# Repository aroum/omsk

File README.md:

# OMSK

OMSK is an experimental, pocket-sized hardware platform designed primarily (but not exclusively) for custom synthesizer firmware development. Built around the RP2350-Zero microcontroller module, OMSK packs an exceptional density of tactile controls, audio routing, and visual indicators into a highly portable footprint.

## Hardware Features

- **MCU:** RP2350-Zero module (or RP2040-Zero)
- **Controls:**
  - 4x4 matrix of Kailh Choc v2 mechanical switches (supports hot-swap sockets)
  - 4 rotary encoders (Alps EC12)
- **Display:** 128x64 OLED screen (supports SH1107 or SSD1312 via I2C)
- **Visuals:** 22 addressable RGB LEDs (WS2812B MINI-E) for parameter tracking and custom animations
- **Audio & Connectivity:**
  - Built-in mono PWM audio output (with optional onboard headphone amplifier circuit)
  - Classic hardware MIDI In/Out jacks (TRS Type A)
  - USB MIDI class-compliant device interface
  - Support for an optional external PCM5102 I2S DAC for high-fidelity stereo audio

For more details on assembly, schematic routing, and BOM, see the [Hardware PCB Guide](hardware/pcb/README.md) and [3D Case/Enclosure Design](hardware/case/README.md).

## Bare-metal Software

All official firmware is written in pure C/C++ using the native Raspberry Pi Pico SDK. There is no Arduino overhead and no RTOS, ensuring maximum CPU availability, bare-metal performance, and sub-millisecond audio and MIDI latency.

### Architecture

Rather than compiling a single monolithic application, OMSK uses separate firmware files for different applications. This separation is dictated by hardware memory limits and fundamental architectural differences:

- Synthesizer engines require different memory structures (e.g., flash space allocated for wavetables and filter LUTs vs. granular sample buffers).
- Audio paths, envelopes, and modulation matrices differ completely between engines.

All firmware targets share a unified low-level core library located in [firmware/shared](firmware/shared), but compile as independent binaries.

> [!NOTE]
> Each firmware folder contains its own documentation and parameter reference: see the respective `README.md` (e.g., [omsk_fm/README.md](firmware/omsk_fm/README.md)) and the `docs/` directory for detailed configuration options (e.g., [omsk_fm/docs](firmware/omsk_fm/docs)). Shared hardware pinouts and peripheral configurations are defined in [firmware/shared/hw_config.h](firmware/shared/hw_config.h) (see [firmware/shared/README.md](firmware/shared/README.md)).

### Firmwares

Explore the firmware directory at [firmware](firmware) to flash any of the following targets:

- **[omsk_wave](firmware/omsk_wave):** A polyphonic wavetable synthesizer featuring deep modulation routing, resonant filters, and non-volatile patch storage.
- **[omsk_grain](firmware/omsk_grain):** A 4-voice granular synthesizer offering real-time grain manipulation, modulation matrices, and full MIDI control.
- **[omsk_fm](firmware/omsk_fm):** An FM (Frequency Modulation) synthesizer engine.
- **[omsk_tracker](firmware/omsk_tracker):** A pocket music tracker and step sequencer to compose patterns and songs directly on the device. [planned]
- **DMK:** A customizable mechanical macropad firmware featuring full Vial compatibility. Remap keys, layout layers, macros, and rotary encoder actions directly from your web browser.
- **[omsk_midi](firmware/omsk_midi):** A simple demonstration firmware that configures the device as a class-compliant USB/TRS MIDI controller.
- **[omsk_oled_test](firmware/omsk_oled_test):** A diagnostic utility to test OLED display functionality, address configuration, and graphics rendering.

Both synth engines support full MIDI CC mapping and preset saving directly to the onboard non-volatile memory.

## Desktop Simulators & Tools

The [`desktop`](desktop) directory contains Python-based software simulators, hardware emulators, and firmware development utilities managed via [`uv`](https://github.com/astral-sh/uv):

- **[`desktop/grain_simulator`](desktop/grain_simulator):** PySide6 GUI simulation of the OMSK Granular Synth engine (`omsk_grain`).
- **[`desktop/synth_simulator`](desktop/synth_simulator):** PySide6 GUI simulation of the OMSK Analog/Wavetable Synth engine (`omsk_synth`).
- **[`desktop/synth_tools`](desktop/synth_tools):** Firmware LUT header generators, hardware emulators (128x64 OLED display, 4x4 matrix keypad), and interactive web testbenches.

Quick launch:

```bash
cd desktop
uv sync
uv run synth_simulator/main.py
```

For more details, see the [Desktop README](desktop/README.md).

## Roadmap & Status

This project is currently a work in progress.

- **Hardware:** Case and knob designs are being actively iterated.
- **Software:** A dedicated web-based editor using WebMIDI is planned to allow quick parameter tweaking, firmware updates, and preset backup/sharing.

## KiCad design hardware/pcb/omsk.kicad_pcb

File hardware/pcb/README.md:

# PCB

## BOM

### Basic

| name                              |  pcs | type          | package | position          | description                      |
| --------------------------------- | ---: | ------------- | ------- | ----------------- | -------------------------------- |
| 1N4148W                           |   17 | Diode         | SOD-323 | D1 - D17          | keyboard matrix + MIDI           |
| 100nF x7r 50v                     |    4 | Capacitor     | 0805    | C1, C3, C4, C5    | MIDI jacks + PWM Audio           |
| 47uF x7r 50v                      |    1 | Capacitor     | 1210    | C2                | PWM audio                        |
| 10R for 3v3 or 220 Ohm for 5v out |    1 | Resistor      | 0603    | R4                | MIDI jacks                       |
| 33R for 3v3 or 220 Ohm for 5v out |    1 | Resistor      | 0603    | R3                | MIDI jacks                       |
| 100R                              |    1 | Resistor      | 0603    | R6                | PWM audio                        |
| 220R                              |    2 | Resistor      | 0603    | R1, R5            | PWM audio + MIDI jacks           |
| 470R                              |    1 | Resistor      | 0603    | R2                | MIDI jacks                       |
| 1.8k                              |    1 | Resistor      | 0603    | R7                | PWM audio                        |
| PJ-313 (3 color)                  |    3 | jack sockets  | THD     | J2, J3, J4        | Audio + MIDI jacks               |
| Alps EC12 8.5 mm                  |    4 | Encoder       | THD     | ROTENC1 - ROTENC4 | Encoder for more info view below |
| H11L1 SMD                         |    1 | Optocoupler   | SOP-6   | U1                | MIDI jacks                       |
| Kailh choc sockets                |   16 | Switch socket | SMD     | SW1 - SW16        | keyboard                         |
| Kailh choc v2                     |   16 | Switch        | THD     | SW1 - SW16        | keyboard                         |
| NC7WZ16P6X                        |    1 | IC            | SC-70-6 | U2                | MIDI jacks + PWM audio           |
| rp2040/rp2350 zero                |    1 | MCU           | Module  | MCU1              | MCU (rp2350 recomended)          |
| WS2812B MINI-E                    |   22 | RGB LED       | 3228SMD | LED1 - LED22      | WS2812B MINI-E                   |

#### Encoders

You can choose any one of the following encoder models:

| name         | torque                 | # of detent/pulses | description |
| ------------ | ---------------------- | -----------------: | ----------- |
| EC12E1220301 | Standard 3 to 20mN･m   |                 12 |             |
| EC12E1240301 | Lightest (jog) 3±2mN･m |                 12 |             |
| EC12E2420301 | Standard 3 to 20mN･m   |                 24 | recommended |
| EC12E2440301 | Lightest (jog) 3±2mN･m |                 24 | recommended |

### Extra

| name                            |  pcs | type    | package | description                                                    |
| ------------------------------- | ---: | ------- | ------- | -------------------------------------------------------------- |
| MIDI cable (DIN5 M to jack 3.5) |    1 | Cable   | Cable   | TRS to DIN5 MIDI cable (Type A) for use external MIDI hardware |
| YS-SK6812MINI-E                 |   22 | RGB LED | 3228SMD | RGB LEDs                                                       |

#### OLED

You can choose any one of the following display models:

| name                             | pcs | type    | package | description |
| -------------------------------- | --- | ------- | ------- | ----------- |
| TZT 1.3" OLED 64×128 i2c SSD1312 | 1   | Display | Module  |             |
| TZT 1.3" OLED 64×128 i2c SH1107  | 1   | Display | Module  | recommended |

##### Pins

| Module pin | MCU pin |
| ---------- | ------- |
| **GND**    | GND     |
| **VCC**    | 3.3V    |
| **SDA**    | GPIO20  |
| **SCL**    | GPIO21  |

#### Headphone amp

Formally, you should not connect headphones directly to the DAC or PWM output without an amplifier; however, in practice, it works fine directly, making an amplifier highly optional. If you decide to use one, you can choose any of the following headphone amplifier models:

| IC                | mW    | size  | price | description |
| ----------------- | ----- | ----- | ----- | ----------- |
| TPA6132           | 25    | S     | 90    |             |
| TDA1308           | 40-80 | S     | 71    |             |
| MAX4410           | 80    | M     | 157   |             |
| MAX97220 +++      | 125   | 20x24 | 225   | tested      |
| OPA1622           | 145   | L     | 113   |             |
| LM4881            | 150   | M     | 60    |             |
| TPA6112 & SGM4812 | 150   | M     | 183   |             |

#### DAC

GY-PCM5102 I2S PCM5102A module

##### Pins

| Module pin | MCU pin / Connection                                        |
| ---------- | ----------------------------------------------------------- |
| **GND**    | GND                                                         |
| **VCC**    | 5V                                                          |
| **BCK**    | GPIO17                                                      |
| **LRCK**   | GPIO18                                                      |
| **DIN**    | GPIO19                                                      |
| **SCK**    | GND (solder jumper next to SCK pin or wire to GND)          |

## Build guide

- Solder all components starting from the lowest profile to the highest in the following order:
  - Diodes
  - Hotswap sockets
  - RGB LEDs
  - For NC7WZ16P6X (U2): the Pin 1 indicator on the IC consists of two dots on the bottom side (where the leftmost dot marks Pin 1), which aligns with the silkscreen tick mark on the PCB footprint.
  - Resistors
  - Capacitors
  - Jacks (recommended colors: green for MIDI IN, yellow for MIDI OUT, black for Audio OUT)
  - H11L1 (U1): the Pin 1 indicator on the IC is a dot on the bottom side, which aligns with the silkscreen tick mark on the PCB footprint.
  - Encoders
  - Solder two jumpers on the board to the `LINE` position (if you plan to use PWM audio).
  - Solder the `5V/3V3` jumper to the required position. This jumper controls the supply voltage of the NC7WZ16P6X (U2) IC. This affects the voltage of the MIDI OUT jack (for 5V, you must change resistors R3-R4 to 220 Ohm) and the PWM audio output level (5V increases the volume significantly, but might introduce noise from the USB power line).
- Connect external modules if needed:
  - **DAC**
    - Solder the jumpers on the back of the module: 1L, 2L, 3H, 4L
    - Solder the jumper bridge next to the SCK pin on the module (bridges SCK to GND to enable internal PLL for 3-wire I2S)
    - Desolder or cut off the audio jack from the module, as it takes too much space and won't fit in the case.
    - Connect using wires:
      - GND on the module to GND on the PCB
      - LOUT on the module to JACK L OUT on the PCB
      - ROUT on the module to JACK R OUT on the PCB
      - VIN to 5V
      - LRCK to GPIO18
      - DIN to GPIO19
      - BCK to GPIO17
      - Solder two jumpers on the board to the `AMP` position
  - **OLED**
    - GND to GND
    - VCC to 3.3V
    - SDA to GPIO20
    - SCL to GPIO21
  - **Headphone amp**
    - GND
    - VCC to 3.3V
    - L- to GND
    - R- to GND
    - L+ to the audio source PWM/DAC LEFT CHANNEL
    - R+ to the audio source PWM/DAC RIGHT CHANNEL
    - LOUT to the audio jack OUT LEFT CHANNEL
    - ROUT to the audio jack OUT RIGHT CHANNEL
    - Solder two jumpers on the board to the `AMP` position
- Assemble the device into the case
- Flash the required firmware

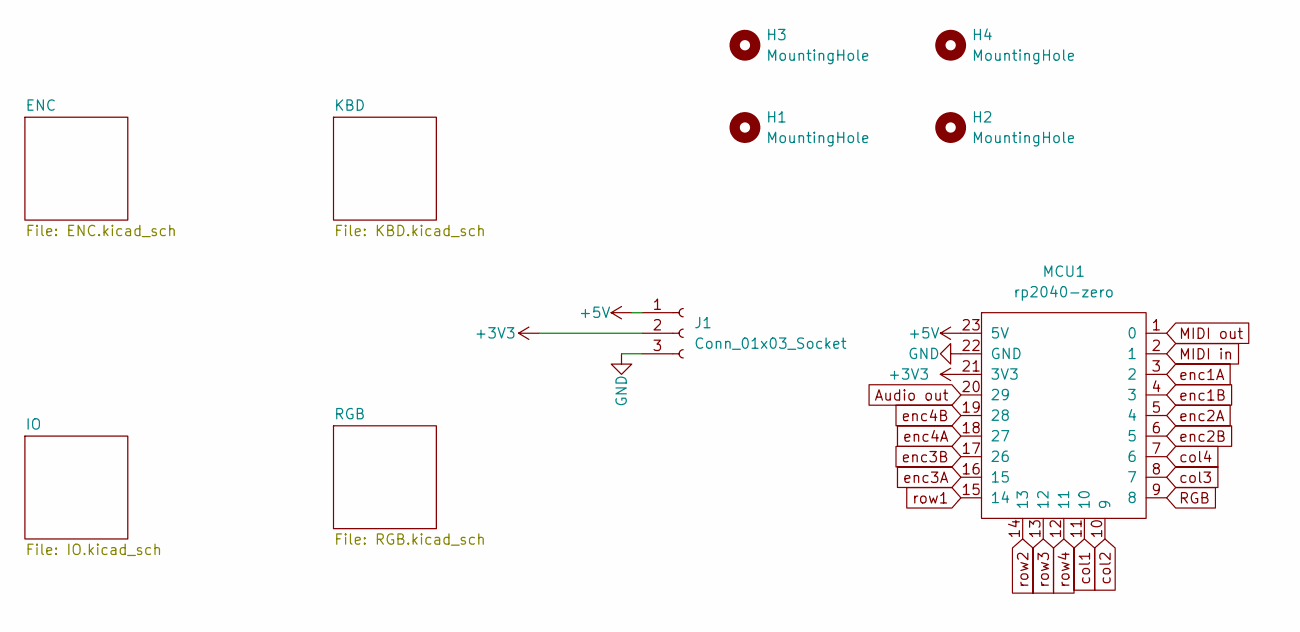
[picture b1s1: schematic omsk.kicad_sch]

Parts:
H1, H2, H3, H4: MountingHole
J1: Conn_01x03_Socket; PinHeader_1x03_P2.54mm_Vertical
MCU1: rp2040-zero; MCU_rp2040-zero

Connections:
+3V3: J1.2, MCU1.21 (3V3); also elsewhere on the board
+5V: J1.1, MCU1.23 (5V); also elsewhere on the board
Audio out: MCU1.20 (29); also elsewhere on the board
GND: J1.3, MCU1.22 (GND); also elsewhere on the board
MIDI in: MCU1.2 (1); also elsewhere on the board
MIDI out: MCU1.1 (0); also elsewhere on the board
RGB: MCU1.9 (8); also elsewhere on the board
col1: MCU1.11 (10); also elsewhere on the board
col2: MCU1.10 (9); also elsewhere on the board
col3: MCU1.8 (7); also elsewhere on the board
col4: MCU1.7 (6); also elsewhere on the board
enc1A: MCU1.3 (2); also elsewhere on the board
enc1B: MCU1.4 (3); also elsewhere on the board
enc2A: MCU1.5 (4); also elsewhere on the board
enc2B: MCU1.6 (5); also elsewhere on the board
enc3A: MCU1.16 (15); also elsewhere on the board
enc3B: MCU1.17 (26); also elsewhere on the board
enc4A: MCU1.18 (27); also elsewhere on the board
enc4B: MCU1.19 (28); also elsewhere on the board
row1: MCU1.15 (14); also elsewhere on the board
row2: MCU1.14 (13); also elsewhere on the board
row3: MCU1.13 (12); also elsewhere on the board
row4: MCU1.12 (11); also elsewhere on the board

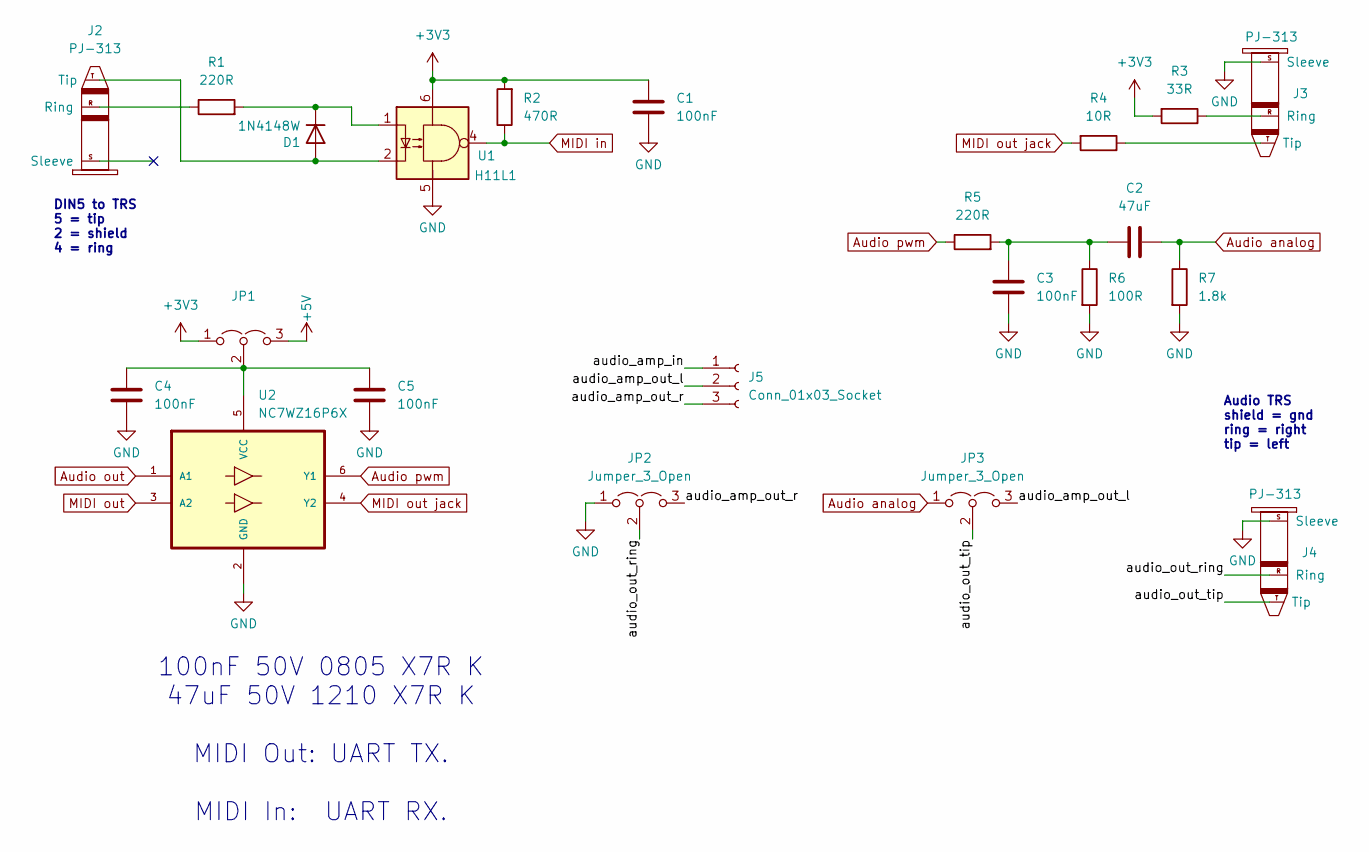
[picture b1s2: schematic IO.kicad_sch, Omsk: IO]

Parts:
C1, C3, C4, C5: 100nF; C_0805_2012Metric_Pad1.18x1.45mm_HandSolder
C2: 47uF; C_1210_3225Metric_Pad1.33x2.70mm_HandSolder
D1: 1N4148W; D_SOD-323_1side
J2, J3, J4: PJ-313; JACK_PJ-313A_1side
J5: Conn_01x03_Socket; PinHeader_1x03_P2.54mm_Vertical
JP1, JP2, JP3: Jumper_3_Open; SolderJumper-3_P1.3mm_Open_RoundedPad1.0x1.5mm
R1, R5: 220R; R_0603_1608Metric_1side
R2: 470R; R_0603_1608Metric_1side
R3: 33R; R_0603_1608Metric_1side
R4: 10R; R_0603_1608Metric_1side
R6: 100R; R_0603_1608Metric_1side
R7: 1.8k; R_0603_1608Metric_1side
U1: H11L1; DIP-6_W8.89mm_SMDSocket_LongPads
U2: NC7WZ16P6X; SOT65P210X110-6N; MPN NC7WZ16P6X

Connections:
+3V3: C1.1, JP1.1 (A), R2.2, R3.2, U1.6; also elsewhere on the board
+5V: JP1.3 (B); also elsewhere on the board
/IO/audio_amp_in: J5.1
/IO/audio_amp_out_l: J5.2, JP3.3 (B)
/IO/audio_amp_out_r: J5.3, JP2.3 (B)
/IO/audio_out_ring: J4.R (Ring), JP2.2 (C)
/IO/audio_out_tip: J4.T (Tip), JP3.2 (C)
Audio analog: C2.2, JP3.1 (A), R7.1
Audio out: U2.1 (A1); also elsewhere on the board
Audio pwm: R5.1, U2.6 (Y1)
GND: C1.2, C3.1, C4.2, C5.2, J3.S (Sleeve), J4.S (Sleeve), JP2.1 (A), R6.2, R7.2, U1.5, U2.2 (GND); also elsewhere on the board
MIDI in: R2.1, U1.4; also elsewhere on the board
MIDI out: U2.3 (A2); also elsewhere on the board
MIDI out jack: R4.2, U2.4 (Y2)
unnamed: C2.1, C3.2, R5.2, R6.1
unnamed: D1.2 (A), J2.T (Tip), U1.2
unnamed: D1.1 (K), R1.2, U1.1
unnamed: J2.R (Ring), R1.1
unnamed: J3.R (Ring), R3.1
unnamed: J3.T (Tip), R4.1
unnamed: C4.1, C5.1, JP1.2 (C), U2.5 (VCC)

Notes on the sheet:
DIN5 to TRS 5 = tip 2 = shield 4 = ring
100nF 50V 0805 X7R K 47uF 50V 1210 X7R K MIDI Out: UART TX. MIDI In: UART RX.
Audio TRS shield = gnd ring = right tip = left

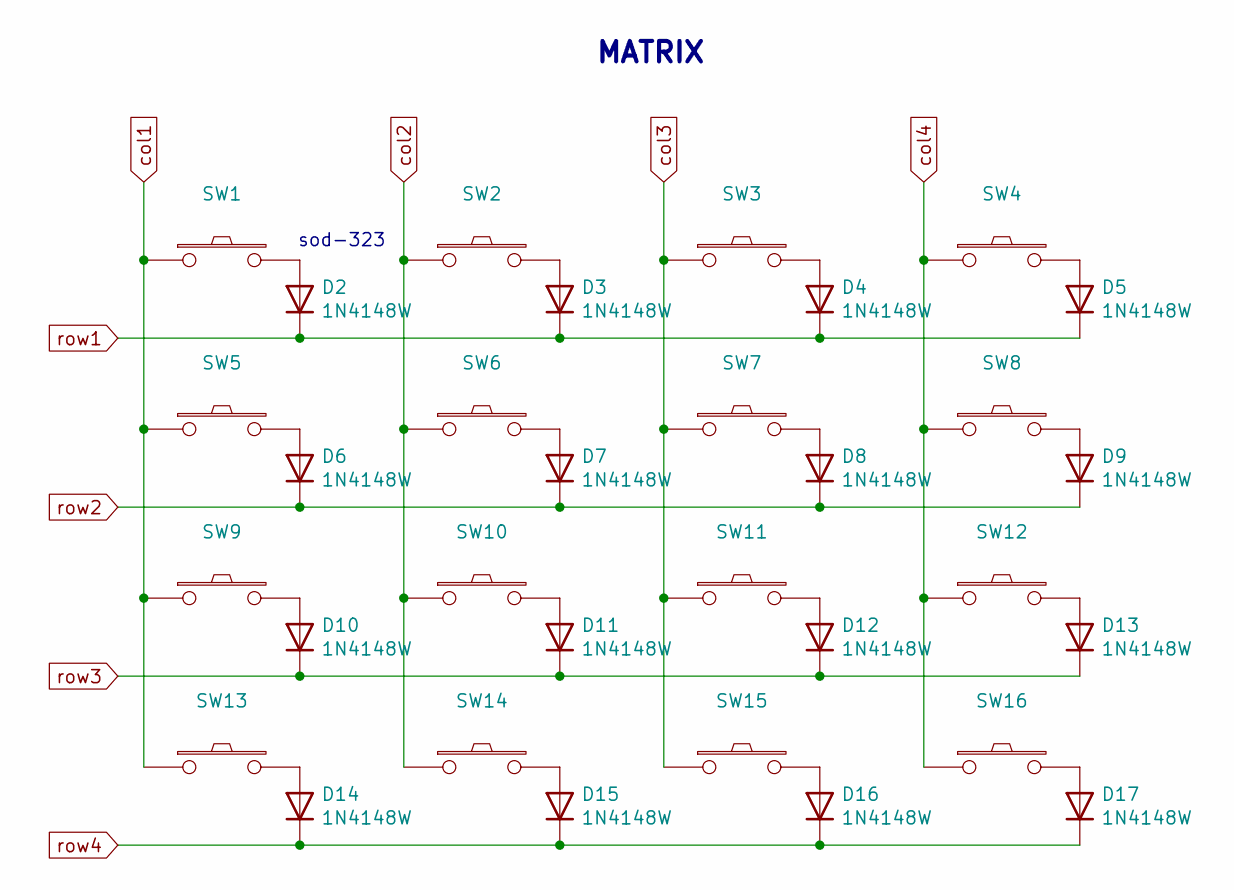
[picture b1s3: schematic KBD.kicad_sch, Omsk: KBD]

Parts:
D2, D3, D4, D5, D6, D7, D8, D9, D10, D11, D12, D13, D14, D15, D16, D17: 1N4148W; D_SOD-323_1side
SW1, SW2, SW3, SW4, SW5, SW6, SW7, SW8, SW9, SW10, SW11, SW12, SW13, SW14, SW15, SW16: SW_PUSH; SW_choc12_hotswap

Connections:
unnamed: D2.2 (A), SW1.2
unnamed: D3.2 (A), SW2.2
unnamed: D4.2 (A), SW3.2
unnamed: D5.2 (A), SW4.2
unnamed: D6.2 (A), SW5.2
unnamed: D7.2 (A), SW6.2
unnamed: D8.2 (A), SW7.2
unnamed: D9.2 (A), SW8.2
unnamed: D10.2 (A), SW9.2
unnamed: D11.2 (A), SW10.2
unnamed: D12.2 (A), SW11.2
unnamed: D13.2 (A), SW12.2
unnamed: D14.2 (A), SW13.2
unnamed: D15.2 (A), SW14.2
unnamed: D16.2 (A), SW15.2
unnamed: D17.2 (A), SW16.2
col1: SW1.1, SW5.1, SW9.1, SW13.1; also elsewhere on the board
col2: SW2.1, SW6.1, SW10.1, SW14.1; also elsewhere on the board
col3: SW3.1, SW7.1, SW11.1, SW15.1; also elsewhere on the board
col4: SW4.1, SW8.1, SW12.1, SW16.1; also elsewhere on the board
row1: D2.1 (K), D3.1 (K), D4.1 (K), D5.1 (K); also elsewhere on the board
row2: D6.1 (K), D7.1 (K), D8.1 (K), D9.1 (K); also elsewhere on the board
row3: D10.1 (K), D11.1 (K), D12.1 (K), D13.1 (K); also elsewhere on the board
row4: D14.1 (K), D15.1 (K), D16.1 (K), D17.1 (K); also elsewhere on the board

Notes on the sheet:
sod-323
MATRIX

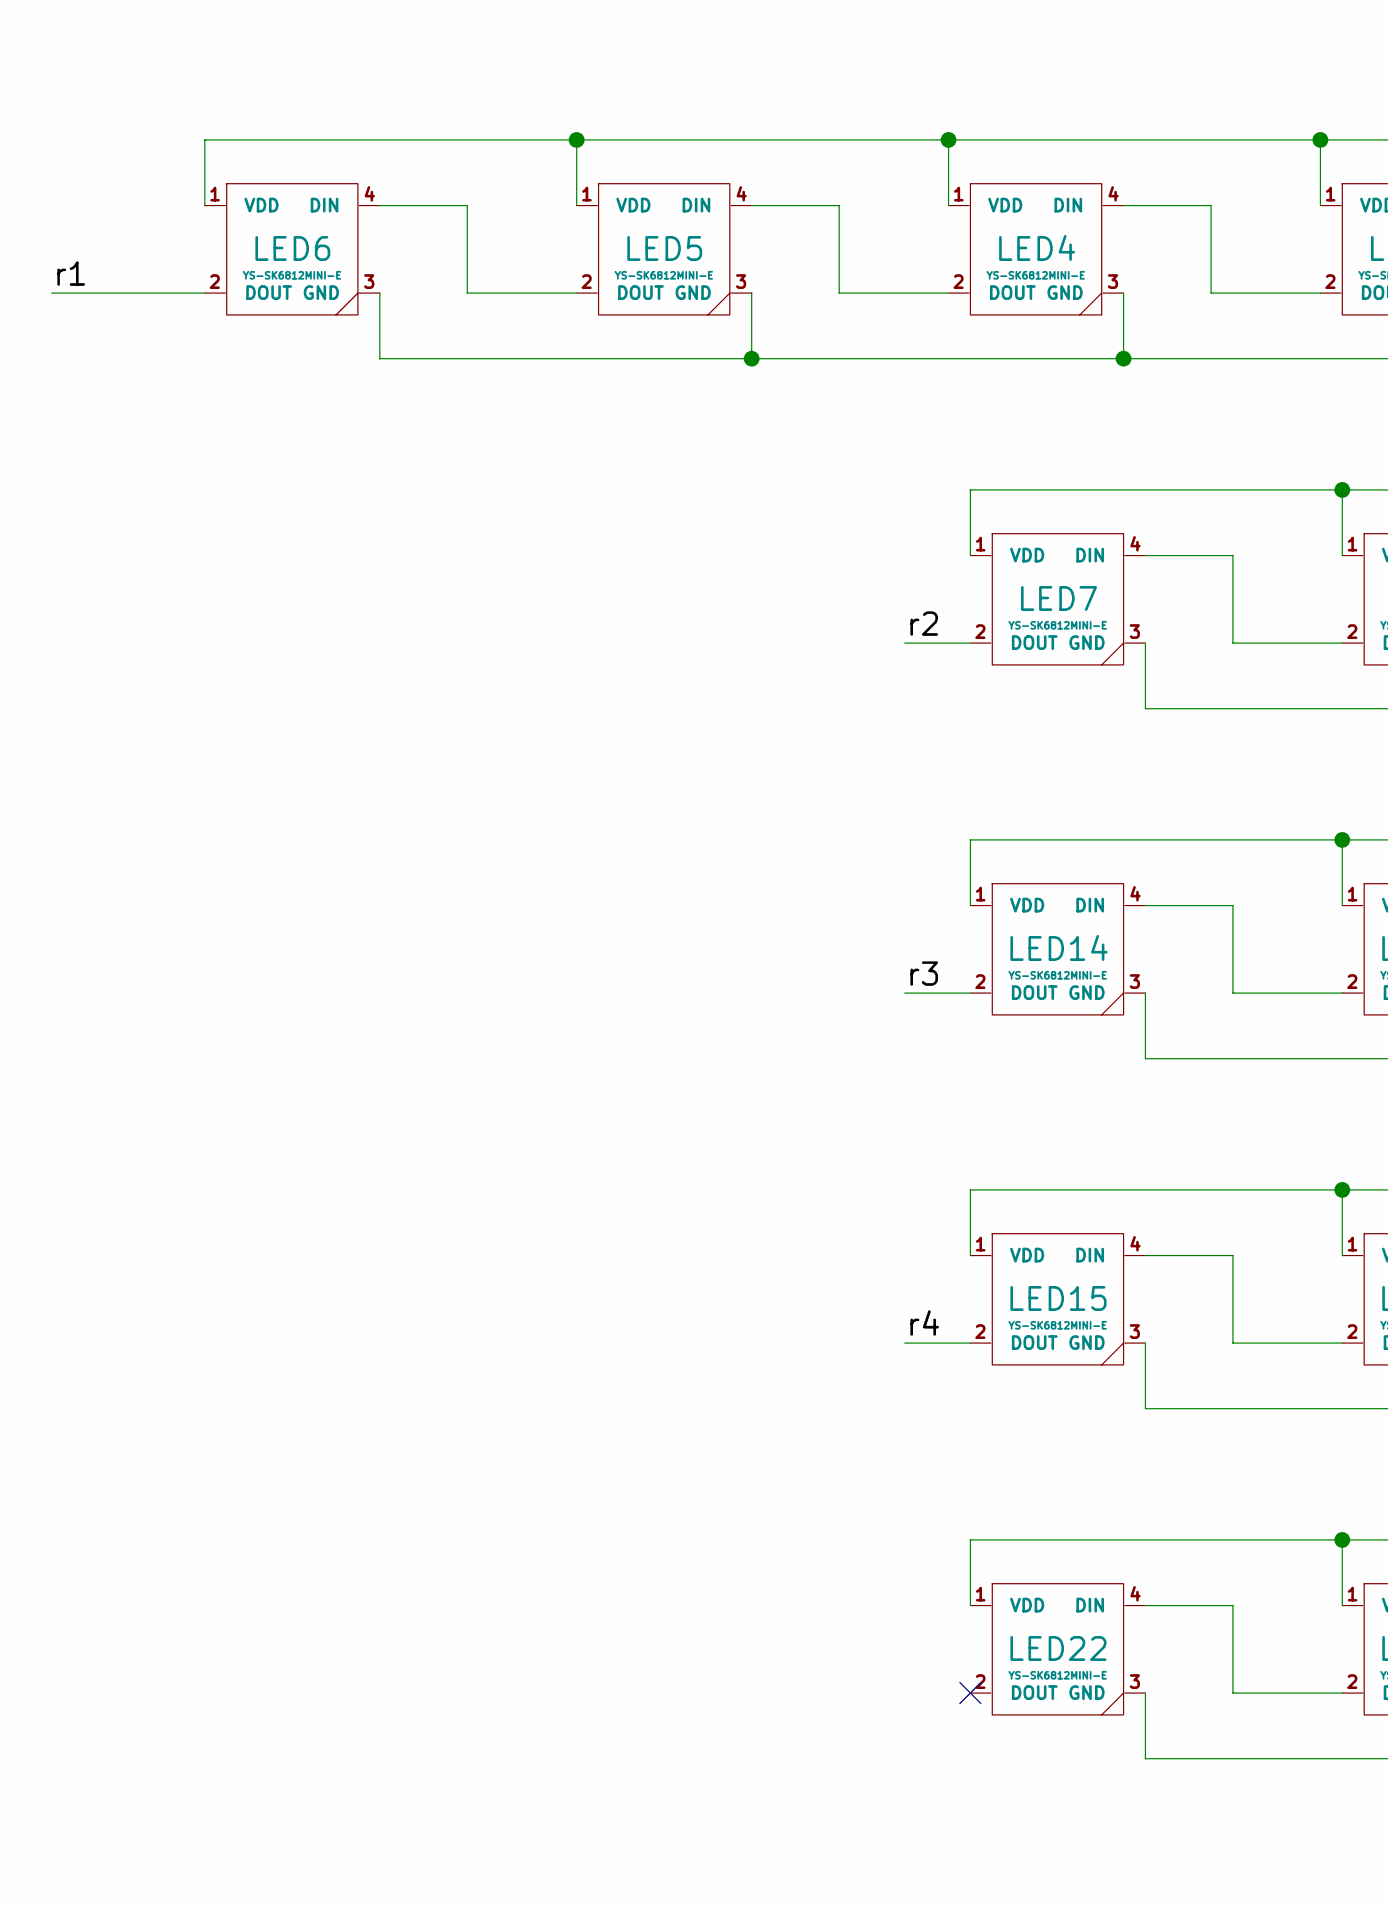
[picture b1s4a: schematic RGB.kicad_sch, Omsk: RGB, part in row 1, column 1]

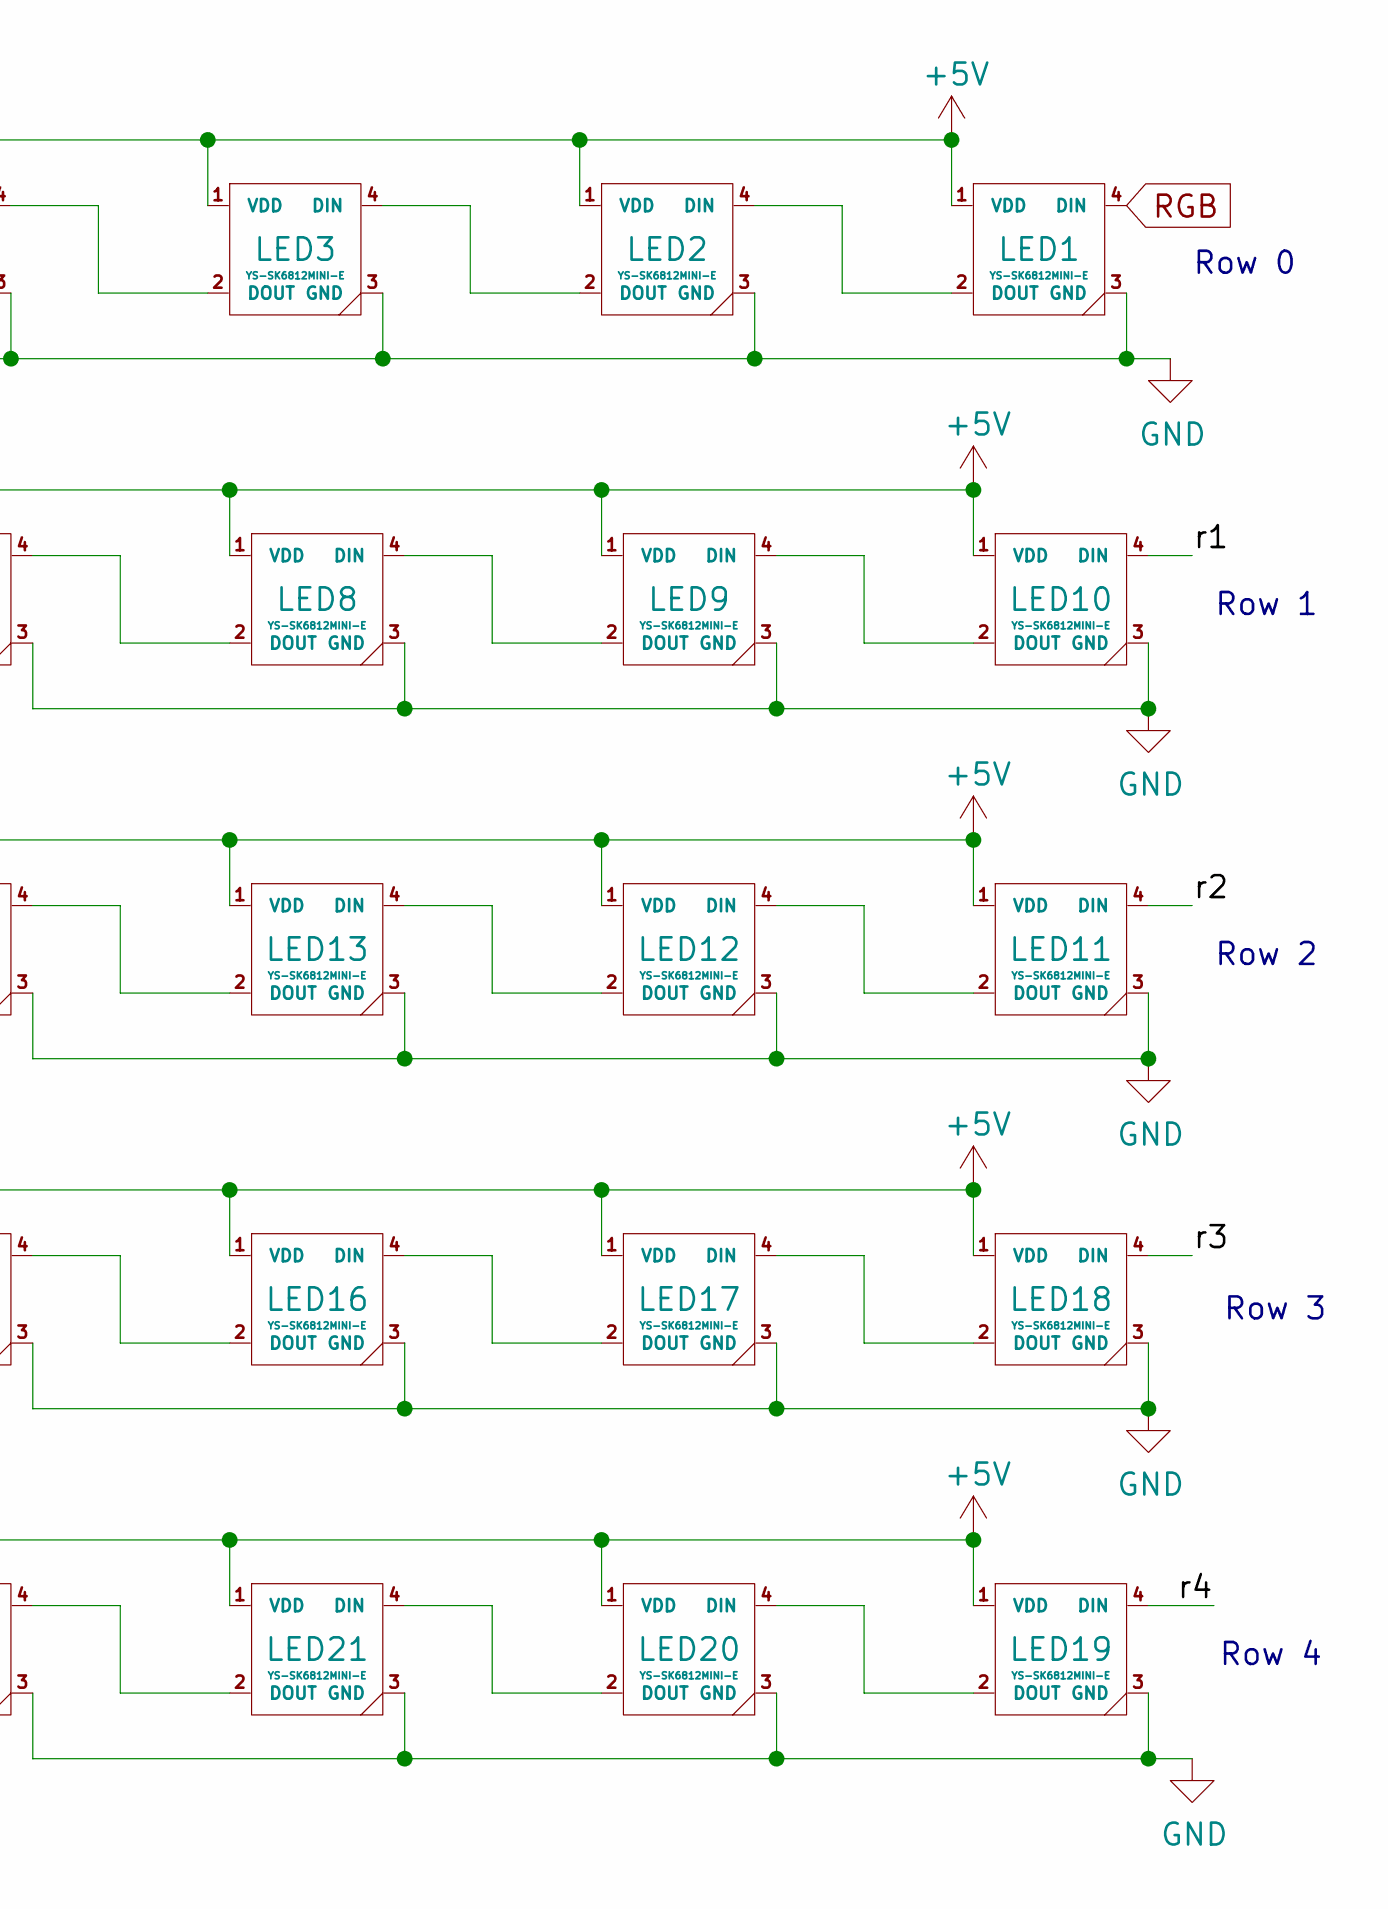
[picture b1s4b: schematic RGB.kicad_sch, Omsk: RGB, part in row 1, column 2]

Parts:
LED1, LED2, LED3, LED4, LED5, LED6, LED7, LED8, LED9, LED10, LED11, LED12, LED13, LED14, LED15, LED16, LED17, LED18, LED19, LED20, LED21, LED22: YS-SK6812MINI-E; LED_YS-SK6812MINI-E_1side

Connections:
+5V: LED1.1 (VDD), LED2.1 (VDD), LED3.1 (VDD), LED4.1 (VDD), LED5.1 (VDD), LED6.1 (VDD), LED7.1 (VDD), LED8.1 (VDD), LED9.1 (VDD), LED10.1 (VDD), LED11.1 (VDD), LED12.1 (VDD), LED13.1 (VDD), LED14.1 (VDD), LED15.1 (VDD), LED16.1 (VDD), LED17.1 (VDD), LED18.1 (VDD), LED19.1 (VDD), LED20.1 (VDD), LED21.1 (VDD), LED22.1 (VDD); also elsewhere on the board
/RGB/r1: LED6.2 (DOUT), LED10.4 (DIN)
/RGB/r2: LED7.2 (DOUT), LED11.4 (DIN)
/RGB/r3: LED14.2 (DOUT), LED18.4 (DIN)
/RGB/r4: LED15.2 (DOUT), LED19.4 (DIN)
GND: LED1.3 (GND), LED2.3 (GND), LED3.3 (GND), LED4.3 (GND), LED5.3 (GND), LED6.3 (GND), LED7.3 (GND), LED8.3 (GND), LED9.3 (GND), LED10.3 (GND), LED11.3 (GND), LED12.3 (GND), LED13.3 (GND), LED14.3 (GND), LED15.3 (GND), LED16.3 (GND), LED17.3 (GND), LED18.3 (GND), LED19.3 (GND), LED20.3 (GND), LED21.3 (GND), LED22.3 (GND); also elsewhere on the board
unnamed: LED1.2 (DOUT), LED2.4 (DIN)
unnamed: LED2.2 (DOUT), LED3.4 (DIN)
unnamed: LED3.2 (DOUT), LED4.4 (DIN)
unnamed: LED4.2 (DOUT), LED5.4 (DIN)
unnamed: LED5.2 (DOUT), LED6.4 (DIN)
unnamed: LED7.4 (DIN), LED8.2 (DOUT)
unnamed: LED8.4 (DIN), LED9.2 (DOUT)
unnamed: LED9.4 (DIN), LED10.2 (DOUT)
unnamed: LED11.2 (DOUT), LED12.4 (DIN)
unnamed: LED12.2 (DOUT), LED13.4 (DIN)
unnamed: LED13.2 (DOUT), LED14.4 (DIN)
unnamed: LED15.4 (DIN), LED16.2 (DOUT)
unnamed: LED16.4 (DIN), LED17.2 (DOUT)
unnamed: LED17.4 (DIN), LED18.2 (DOUT)
unnamed: LED19.2 (DOUT), LED20.4 (DIN)
unnamed: LED20.2 (DOUT), LED21.4 (DIN)
unnamed: LED21.2 (DOUT), LED22.4 (DIN)
RGB: LED1.4 (DIN); also elsewhere on the board

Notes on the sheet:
Row 2
Row 0
Row 1
Row 4
Row 3

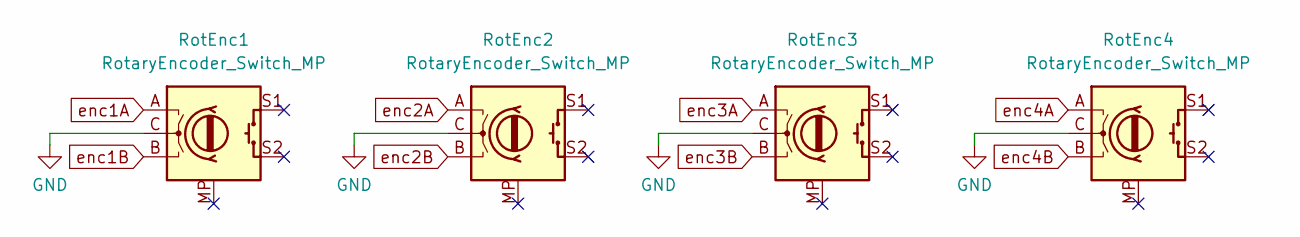
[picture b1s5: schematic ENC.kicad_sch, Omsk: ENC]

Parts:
RotEnc1, RotEnc2, RotEnc3, RotEnc4: RotaryEncoder_Switch_MP; RotEnc_Alps_EC12E-SWitch_Vertical_H20mm-without_SW

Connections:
GND: RotEnc1.C, RotEnc2.C, RotEnc3.C, RotEnc4.C; also elsewhere on the board
enc1A: RotEnc1.A; also elsewhere on the board
enc1B: RotEnc1.B; also elsewhere on the board
enc2A: RotEnc2.A; also elsewhere on the board
enc2B: RotEnc2.B; also elsewhere on the board
enc3A: RotEnc3.A; also elsewhere on the board
enc3B: RotEnc3.B; also elsewhere on the board
enc4A: RotEnc4.A; also elsewhere on the board
enc4B: RotEnc4.B; also elsewhere on the board

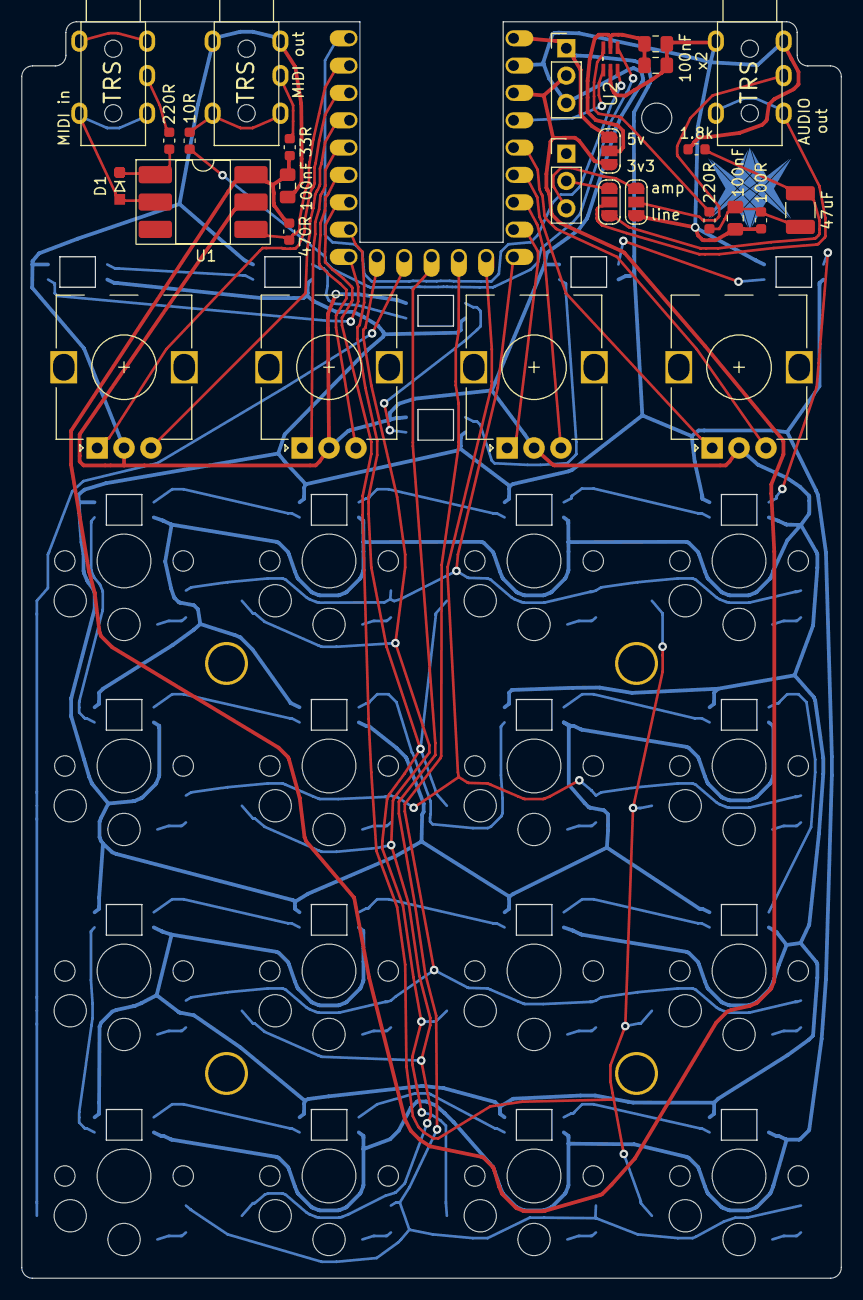
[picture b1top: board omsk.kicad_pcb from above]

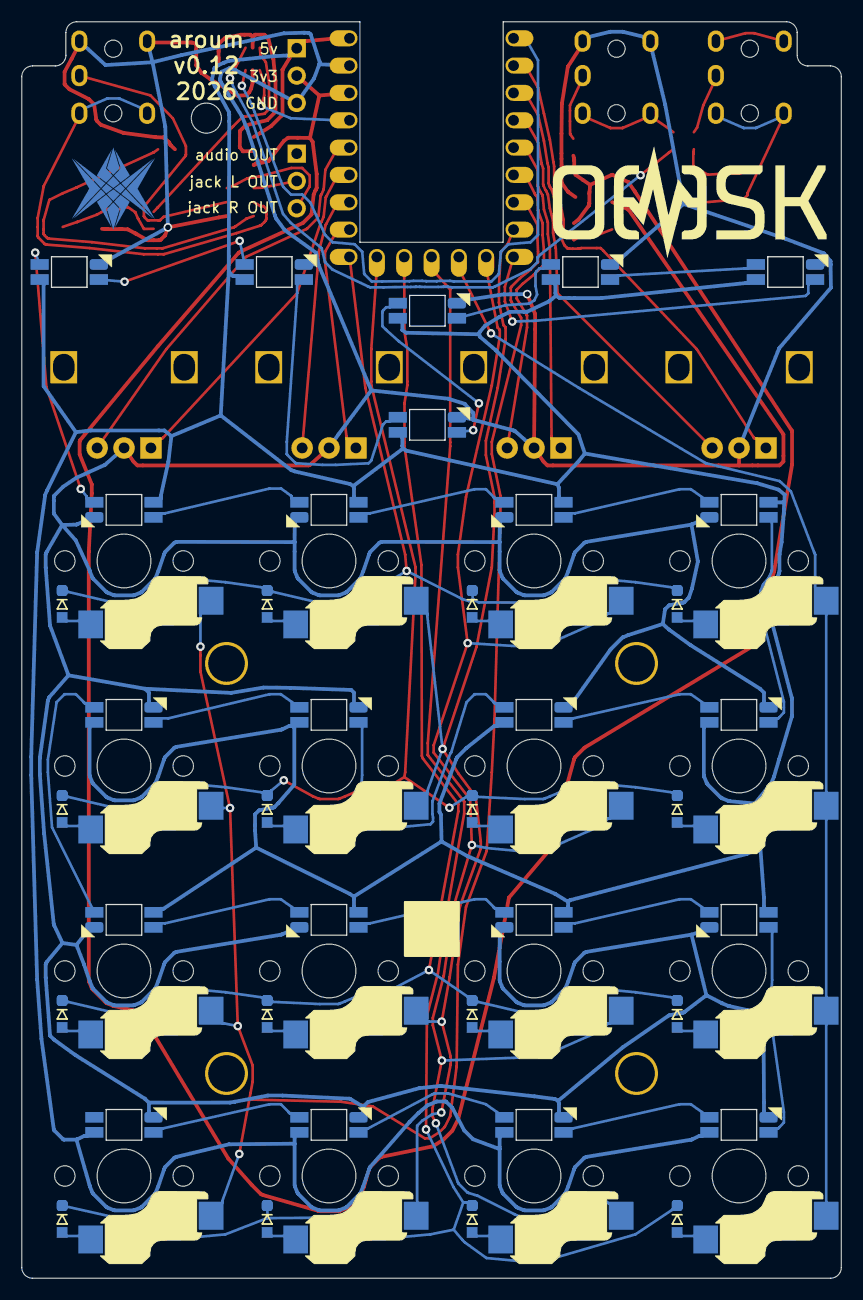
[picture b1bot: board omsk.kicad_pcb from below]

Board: 2 copper layers, 76.1 x 116.7 mm, 88 parts (44 on the bottom side), 74 nets.

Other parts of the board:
G1, G43: LOGO
